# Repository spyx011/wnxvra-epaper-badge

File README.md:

# WNXVRA E-Paper Badge

A wearable name badge with a 2.9" e-paper display, an ESP32-S3, USB-C charging and a LiPo battery.
The board is shaped like a classic conference badge: chamfered corners, a second panel on the right
joined by two tabs, gold (ENIG) ornaments, and big gold lettering. The battery sits on the back of the right panel.

## Features
- **ESP32-S3-MINI-1**: Wi-Fi, Bluetooth LE, native USB
- **2.9" e-paper** (296 x 128, black/white, GDEY029T94 with SSD1680), 24-pin 0.5 mm FPC
- **USB-C charging** with an MCP73831 (about 196 mA) and a single-cell LiPo (503040, 500 mAh)
- **3.3 V LDO** (AP2112K-3.3); the display supply is switched off by a P-MOSFET during deep sleep
- **5 buttons**: RESET, BOOT, and three user buttons (A, B, C)
- **Gold artwork and lettering** (WNXVRA on the front, @WNXVRA on the back), made of exposed copper

The e-paper panel needs higher voltages than 3.3 V, so the board has the standard boost circuit
(MOSFET, 47 uH inductor, Schottky diodes and a negative charge pump). Cutting its supply in deep sleep saves battery.
The panel holds its image with no power.

## Bill of materials
48 parts on the board, plus the display and battery. Full list: [`bom/badge_bom.csv`](badge_bom_prices.csv).

##CAD 
3 CAD files one for the base, one for the cover and one for the buttons: [`.STEP`](.STEP).
https://cad.onshape.com/documents/018a6b643a004c4ffecb9c05/w/87c0a5966f5afdf6ff250c8b/e/41b2493d74fe29fee25ded77

## Assembly notes
- Check the LiPo plug polarity against J2 before connecting a battery. Cells from different sellers are wired differently.
- Stick the battery to the back of the right panel with double-sided tape, inside the marked outline.
- The two tabs between the panels carry the battery wires. Don't break them off unless you move the battery connector.
- Hold BOOT and tap RESET to enter USB download mode.

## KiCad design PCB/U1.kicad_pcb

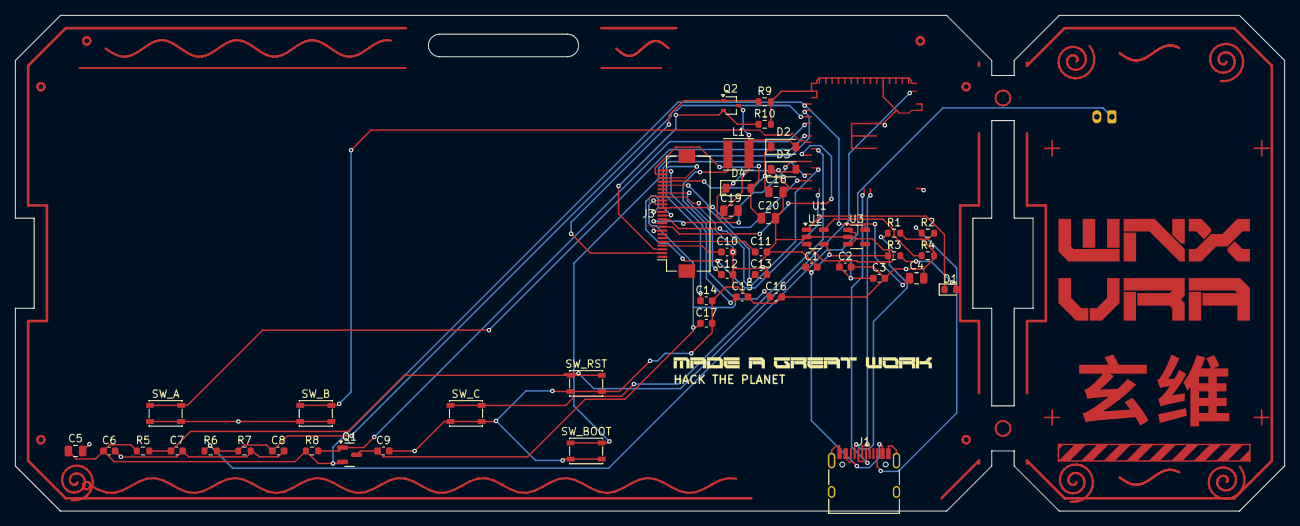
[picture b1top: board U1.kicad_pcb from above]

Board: 2 copper layers, 169.0 x 66.0 mm, 47 parts (1 on the bottom side), 27 nets.

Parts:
C1, C2, C9: 4.7uF; C_0603_1608Metric
C3, C7, C10, C11, C12, C13, C14, C15, C16: 1uF; C_0603_1608Metric
C4, C5: 10uF; C_0805_2012Metric
C6, C8, C17: 100nF; C_0603_1608Metric
C18, C19, C20: 1uF/50V; C_0805_2012Metric
D1: CHG; LED_0603_1608Metric
D2, D3, D4: MBR0530; D_SOD-123
J1: USB-C; USB_C_Receptacle_HRO_TYPE-C-31-M-12
J2: LiPo (check polarity!); JST_PH_B2B-PH-K_1x02_P2.00mm_Vertical
J3: EPD_2.9in_FPC; Hirose_FH12-24S-0.5SH_1x24-1MP_P0.50mm_Horizontal
L1: 47uH; L_Taiyo-Yuden_NR-40xx
Q1: P-MOSFET (SOT-23); SOT-23
Q2: Si1308EDL; SOT-323_SC-70
R1, R2, R4: 5.1k; R_0603_1608Metric
R3: 1k; R_0603_1608Metric
R5, R9: 10k; R_0603_1608Metric
R6, R7: 220k; R_0603_1608Metric
R8: 100k; R_0603_1608Metric
R10: 3R; R_0603_1608Metric
SW_A: SW_Push; SW_SPST_PTS810
SW_B: SW_Push; SW_SPST_PTS810
SW_BOOT: SW_Push; SW_SPST_PTS810
SW_C: SW_Push; SW_SPST_PTS810
SW_RST: SW_Push; SW_SPST_PTS810
U2: MCP73831-2-OT; SOT-23-5
U3: AP2112K-3.3; SOT-23-5

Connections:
+3V3: C4.1, C5.1, C6.1, Q1.2, R5.1, R8.1, U3.5
+BATT: C2.1, C3.1, J2.1, R6.1, U2.3, U3.1, U3.3
CC1: J1.A5, R1.1
CC2: J1.B5, R2.1
CHG_STAT: D1.1, U2.1
EN: C7.1, R5.2, SW_RST.1
EPD_PWR_EN: Q1.1, R8.2
EPD_VCC: C9.1, C16.1, C17.1, J3.15, J3.16, L1.1, Q1.3
EPD_VCOM: C15.1, J3.24
EPD_VDD: C12.1, J3.18
EPD_VGH: C11.1, J3.5
EPD_VGL: C10.1, J3.4
EPD_VSH: C13.1, J3.20
EPD_VSL: C14.1, J3.22
GDR: J3.2, Q2.1, R9.1
GND: C1.2, C2.2, C3.2, C4.2, C5.2, C6.2, C7.2, C8.2, C9.2, C10.2, C11.2, C12.2, C13.2, C14.2, C15.2, C16.2, C17.2, C18.2, C20.2, D3.1, J1.A1, J1.A12, J1.B1, J1.B12, J1.S1, J2.2, J3.8, J3.17, R1.2, R2.2, R4.2, R7.2, R9.2, R10.2, SW_A.2, SW_B.2, SW_BOOT.2, SW_C.2, SW_RST.2, U2.2, U3.2
LED_A: D1.2, R3.2
PREVGH: C18.1, D2.1, J3.21
PREVGL: C20.1, D4.2, J3.23
PROG: R4.1, U2.5
PUMP_Z: C19.2, D3.2, D4.1
RESE: J3.3, Q2.2, R10.1
SW_NODE: C19.1, D2.2, L1.2, Q2.3
USB_DM: J1.A7, J1.B7
USB_DP: J1.A6, J1.B6
VBAT_SENSE: C8.1, R6.2, R7.1
VBUS: C1.1, J1.A4, J1.A9, J1.B4, J1.B9, R3.1, U2.4

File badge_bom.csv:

Qty,Designators,Value,Part number,LCSC,Unit USD,Line USD,Price status,Purchase link,Link type
1.0,U1,ESP32-S3 module,ESP32-S3-MINI-1-N8,C2913206,4.50,4.5,checked,https://www.lcsc.com/search?q=C2913206,LCSC search
1.0,U2,LiPo charger,MCP73831T-2ATI/OT,C14879,1.00,1.0,checked (0.93-1.27 at qty 1),https://www.lcsc.com/search?q=C14879,LCSC search
1.0,U3,3.3 V regulator,AP2112K-3.3TRG1,C51118,0.20,0.2,estimate,https://www.lcsc.com/search?q=C51118,LCSC search
1.0,J1,USB-C port,TYPE-C-31-M-12,C165948,0.20,0.2,estimate,https://www.lcsc.com/search?q=C165948,LCSC search
1.0,J2,Battery connector,B2B-PH-K-S,,0.15,0.15,estimate,https://www.lcsc.com/search?q=B2B-PH-K-S,LCSC search
1.0,J3,Display connector (FPC),FH12-24S-0.5SH(55),C202112,0.50,0.5,checked,https://www.lcsc.com/search?q=C202112,LCSC search
1.0,Q1,P-MOSFET,AO3401A,,0.05,0.05,estimate,https://www.lcsc.com/search?q=AO3401A,LCSC search
1.0,Q2,N-MOSFET,SI1308EDL-T1-GE3,C469327,0.45,0.45,estimate,https://www.lcsc.com/search?q=C469327,LCSC search
3.0,D2 D3 D4,Schottky diode,MBR0530,C699108,0.04,0.12,estimate,https://www.lcsc.com/search?q=C699108,LCSC search
1.0,D1,Charge LED,0603 red LED,,0.03,0.03,estimate,https://www.lcsc.com/search?q=0603%20red%20LED,LCSC search
1.0,L1,47 uH inductor,NR4018T470M,,0.35,0.35,estimate,https://www.lcsc.com/search?q=NR4018T470M,LCSC search
5.0,SW_RST SW_BOOT SW_A SW_B SW_C,Tactile button,PTS810,,0.20,1.0,estimate,https://www.lcsc.com/search?q=PTS810,LCSC search
10.0,R1-R10,Resistors 0603 (5 values),generic,,0.01,0.1,estimate,https://www.lcsc.com/search?q=generic,LCSC search
3.0,C6 C8 C17,100 nF 0603,generic,,0.01,0.03,estimate,https://www.lcsc.com/search?q=generic,LCSC search
9.0,C3 C7 C10-C16,1 uF 0603,generic,,0.02,0.18,estimate,https://www.lcsc.com/search?q=generic,LCSC search
3.0,C1 C2 C9,4.7 uF 0603,generic,,0.04,0.12,estimate,https://www.lcsc.com/search?q=generic,LCSC search
2.0,C4 C5,10 uF 0805,generic,,0.05,0.1,estimate,https://www.lcsc.com/search?q=generic,LCSC search
3.0,C18 C19 C20,1 uF 50 V 0805,generic,,0.05,0.15,estimate,https://www.lcsc.com/search?q=generic,LCSC search
1.0,(PCB),"Bare PCB 169x66 mm, 2-layer, 1.6 mm, ENIG",JLCPCB (about $25 for 5 boards),,5.00,5.0,estimate (range 4-7 per board),https://www.lcsc.com/search?q=JLCPCB%20%28about%20%2425%20fo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,LCSC search
1.0,(display),2.9in e-paper,GDEY029T94,,8.70,8.7,checked,https://www.lcsc.com/search?q=GDEY029T94,LCSC search
1.0,(battery),LiPo 3.7 V 500 mAh 503040,with protection + JST PH,,5.00,5.0,estimate,https://www.lcsc.com/search?q=with%20protection%20%2B%20JST%20PH,LCSC search
,,,,,TOTAL per badge (before shipping),27.93,,,
,,TOTAL,,,,27.93,"Estimate; excludes shipping, taxes and assembly",,
